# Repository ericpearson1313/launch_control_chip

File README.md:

# launch_chip
A model rocket launch control chip. A better push button?

## Datasheet
Semiconductors start out as an idea. Early datasheets allow exploration of the functionallity to meet the system need.
I've created a mock datasheet for a launch control chip, to both inspire and try to ground my design as a practical device with multiple applications.
Key functions and parameters set and documented. A compact module was defined which encompassed core functionallity centered around the device. Considering
multiple applications for this module firmed up the I/O to ease integration with clean schematics for each situation. A development board was then designed,
fully integration the LCC into a single board handheld lauch controller, and enabling chip development.

[Datasheet](Launch_chip_arch.pdf)

## Development Board PCB Design
Guided by the datasheet thought process the development board PCB was designed. The KiCad schematic and pcb have been developed and added to the repo.
The design will be revisioned until tapeout release. I'll use this board to bring up the LCC.

[KiCAD Project](dev_board.kicad_pro)

[KiCAD Schematic](dev_board.kicad_sch)

[KiCAD PCB](dev_board.kicad_pcb)

[Bill of Materials](dev_board.csv)

## Datasheet Snapshots

#### Extra prototype devices 

I have finished development of my 'perfect?' handheld launch controller powered by the launch control chip. Of the prototype run of devices I have a few extra, and have listed them for sale at cost on Ebay for an offer of $35, with free lettermail shipping. If you have followed the same technical direction as myself, I know this chip would have helped me alot, so maybe it could help other similar hobby technical enthusiasts. [LCC-01 Ebay listing](https://www.ebay.ca/itm/157937950540)

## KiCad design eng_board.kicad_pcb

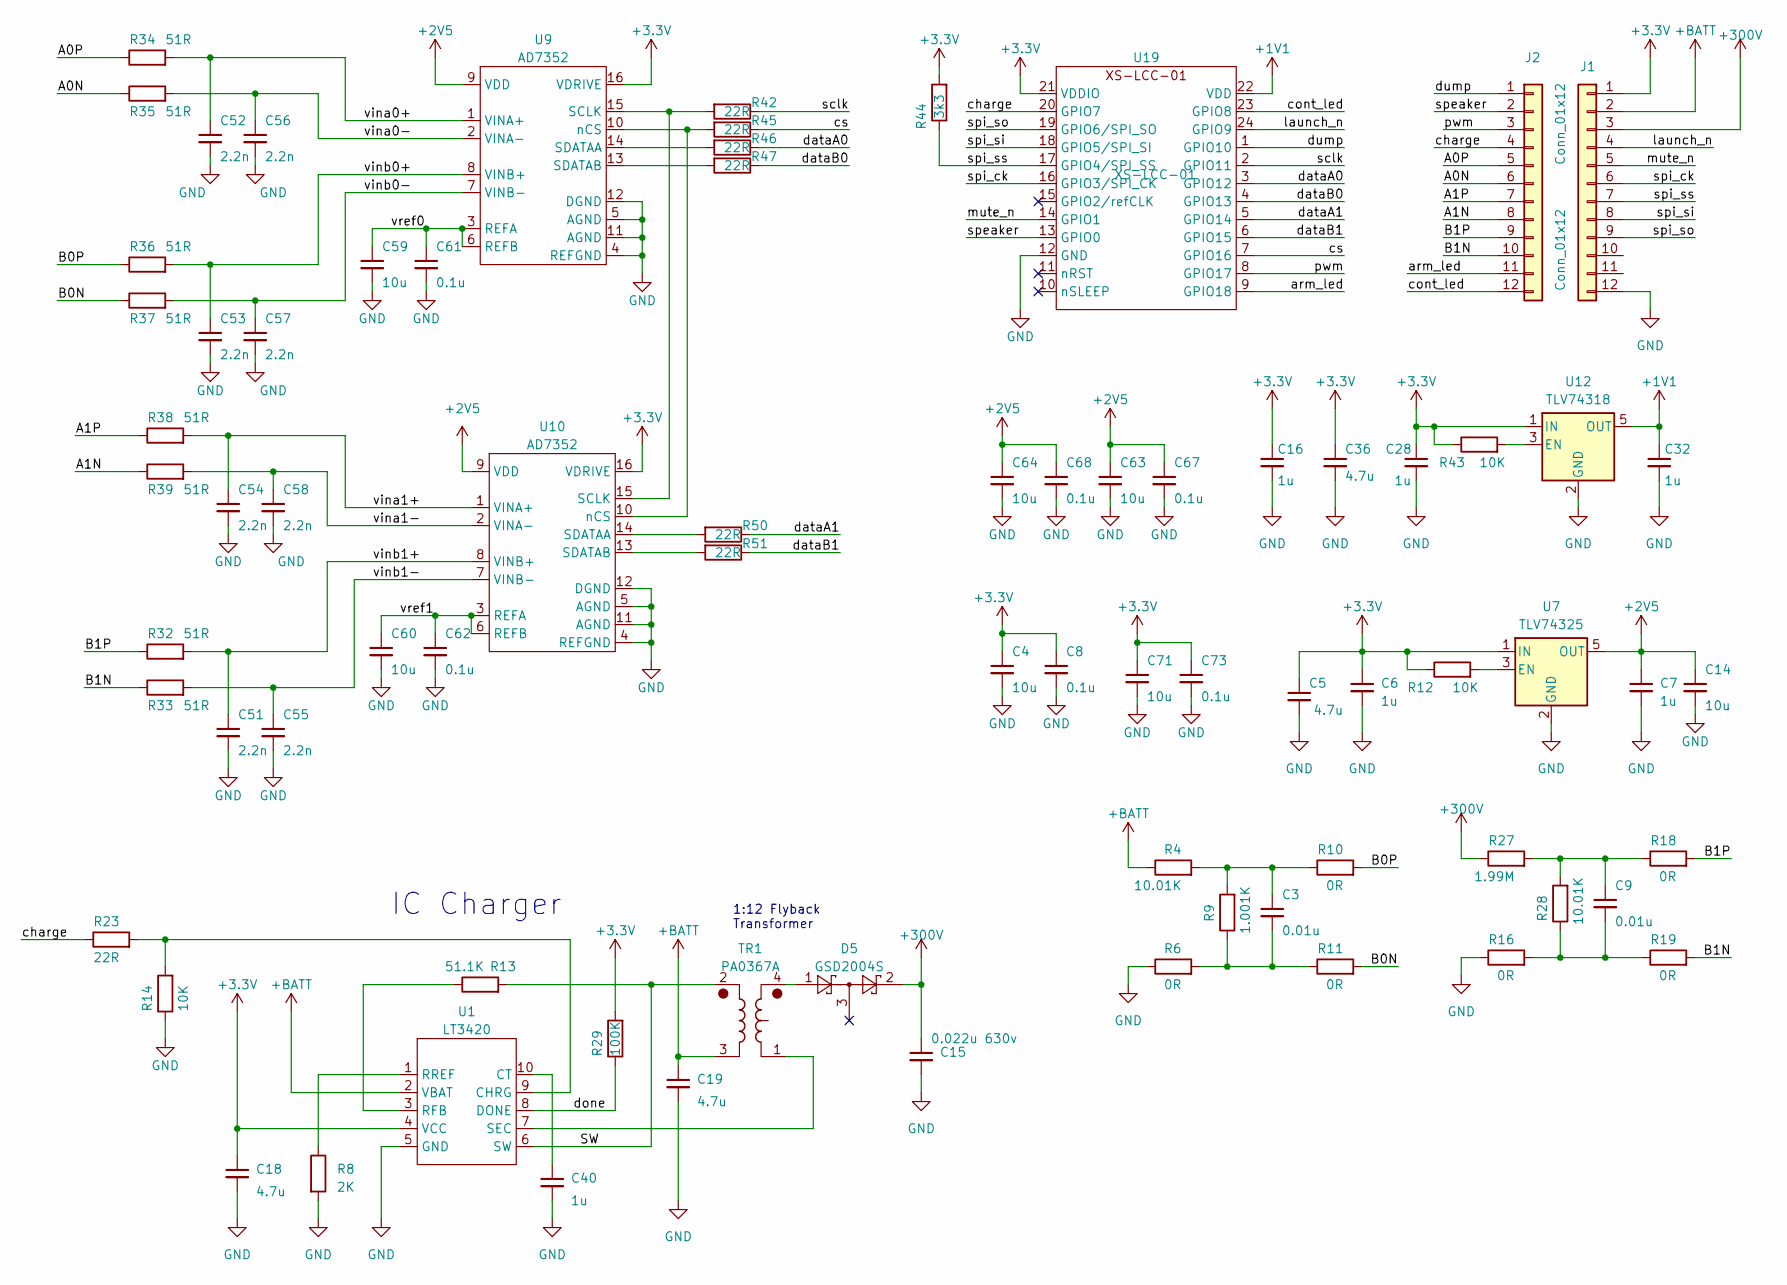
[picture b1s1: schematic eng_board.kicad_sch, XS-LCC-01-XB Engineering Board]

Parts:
C3, C9: 0.01u; C_0603_1608Metric
C4, C14, C59, C60, C63, C64, C71: 10u; C_1206_3216Metric
C5, C18, C19, C36: 4.7u; C_1206_3216Metric
C6, C7, C16, C28, C32, C40: 1u; C_0603_1608Metric
C8, C61, C62, C67, C68, C73: 0.1u; C_0603_1608Metric
C15: 0.022u 630v; C_1206_3216Metric
C51, C52, C53, C54, C55, C56, C57, C58: 2.2n; C_0603_1608Metric
D5: GSD2004S; SOT-23; JLC C85606
J1, J2: Conn_01x12; PinHeader_1x12_P2.54mm_Vertical
R4, R28: 10.01K; R_0603_1608Metric; JLC C778416
R6, R10, R11, R16, R18, R19: 0R; R_0603_1608Metric; JLC C778416
R8: 2K; R_0603_1608Metric; JLC C319700
R9: 1.001K; R_0603_1608Metric; JLC C778416
R12, R43: 10K; R_0603_1608Metric; JLC C778416
R13: 51.1K; R_0603_1608Metric; JLC C234563
R14: 10K; R_0603_1608Metric; JLC C491211
R23: 22R; R_0603_1608Metric; JLC C778416
R27: 1.99M; R_0603_1608Metric; JLC C778416
R29: 100K; R_0603_1608Metric; JLC C319967
R32, R33, R34, R35, R36, R37, R38, R39: 51R; R_0603_1608Metric; JLC C778416
R42, R45, R46, R47, R50, R51: 22R; R_0603_1608Metric; JLC C319967
R44: 3k3; R_0603_1608Metric; JLC C319967
TR1: PA0367A; PA0637A Pulse Coil 3D; JLC C5382098
U1: LT3420; MSOP-10_3x3mm_P0.5mm; JLC C670531
U7: TLV74325; SOT-23-5
U9, U10: AD7352; TSSOP-16_4.4x5mm_P0.65mm
U12: TLV74318; SOT-23-5
U19: XS-LCC-01; QFN-24-3x3mm

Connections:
+1V1: C32.1, U12.5 (OUT), U19.22 (VDD)
+2V5: C7.1, C14.1, C63.1, C64.1, C67.1, C68.1, U7.5 (OUT), U9.9 (VDD), U10.9 (VDD)
+3.3V: C4.1, C5.1, C6.1, C8.1, C16.1, C18.1, C28.1, C36.1, C71.1, C73.1, J1.1, R12.1, R29.2, R43.1, R44.2, U1.4 (VCC), U7.1 (IN), U9.16 (VDRIVE), U10.16 (VDRIVE), U12.1 (IN), U19.21 (VDDIO)
+300V: C15.1, D5.2 (NC), J1.3, R27.1
+BATT: C19.1, J1.2, R4.1, TR1.3, U1.2 (VBAT)
/A0N: J2.6, R35.1
/A0P: J2.5, R34.1
/A1N: J2.8, R39.1
/A1P: J2.7, R38.1
/B0N: R11.2, R37.1
/B0P: R10.2, R36.1
/B1N: J2.10, R19.2, R33.1
/B1P: J2.9, R18.2, R32.1
/SW: R13.2, TR1.2, U1.6 (SW)
/arm_led: J2.11, U19.9 (GPIO18)
/charge: J2.4, R23.1, U19.20 (GPIO7)
/cont_led: J2.12, U19.23 (GPIO8)
/cs: R45.1, U19.7 (GPIO16)
/dataA0: R46.1, U19.3 (GPIO12)
/dataA1: R50.1, U19.5 (GPIO14)
/dataB0: R47.1, U19.4 (GPIO13)
/dataB1: R51.1, U19.6 (GPIO15)
/done: R29.1, U1.8 (DONE)
/dump: J2.1, U19.1 (GPIO10)
/launch_n: J1.4, U19.24 (GPIO9)
/mute_n: J1.5, U19.14 (GPIO1)
/pwm: J2.3, U19.8 (GPIO17)
/sclk: R42.1, U19.2 (GPIO11)
/speaker: J2.2, U19.13 (GPIO0)
/spi_ck: J1.6, U19.16 (GPIO3/SPI_CK)
/spi_si: J1.8, U19.18 (GPIO5/SPI_SI)
/spi_so: J1.9, U19.19 (GPIO6/SPI_SO)
/spi_ss: J1.7, R44.1, U19.17 (GPIO4/SPI_SS)
/vina0+: C52.1, R34.2, U9.1 (VINA+)
/vina0-: C56.1, R35.2, U9.2 (VINA-)
/vina1+: C54.1, R38.2, U10.1 (VINA+)
/vina1-: C58.1, R39.2, U10.2 (VINA-)
/vinb0+: C53.1, R36.2, U9.8 (VINB+)
/vinb0-: C57.1, R37.2, U9.7 (VINB-)
/vinb1+: C51.1, R32.2, U10.8 (VINB+)
/vinb1-: C55.1, R33.2, U10.7 (VINB-)
/vref0: C59.1, C61.1, U9.3 (REFA), U9.6 (REFB)
/vref1: C60.1, C62.1, U10.3 (REFA), U10.6 (REFB)
GND: C4.2, C5.2, C6.2, C7.2, C8.2, C14.2, C15.2, C16.2, C18.2, C19.2, C28.2, C32.2, C36.2, C40.2, C51.2, C52.2, C53.2, C54.2, C55.2, C56.2, C57.2, C58.2, C59.2, C60.2, C61.2, C62.2, C63.2, C64.2, C67.2, C68.2, C71.2, C73.2, J1.12, R6.1, R8.2, R14.1, R16.1, U1.5 (GND), U7.2 (GND), U9.4 (REFGND), U9.5 (AGND), U9.11 (AGND), U9.12 (DGND), U10.4 (REFGND), U10.5 (AGND), U10.11 (AGND), U10.12 (DGND), U12.2 (GND), U19.12 (GND)
unnamed: C3.1, R4.2, R9.2, R10.1
unnamed: C3.2, R6.2, R9.1, R11.1
unnamed: C9.1, R18.1, R27.2, R28.2
unnamed: C9.2, R16.2, R19.1, R28.1
unnamed: D5.1, TR1.4
unnamed: R14.2, R23.2, U1.9 (CHRG)
unnamed: C40.1, U1.10 (CT)
unnamed: R13.1, U1.3 (RFB)
unnamed: R8.1, U1.1 (RREF)
unnamed: TR1.1, U1.7 (SEC)
unnamed: R12.2, U7.3 (EN)
unnamed: R46.2, U9.14 (SDATAA)
unnamed: R47.2, U9.13 (SDATAB)
unnamed: R42.2, U9.15 (SCLK), U10.15 (SCLK)
unnamed: R50.2, U10.14 (SDATAA)
unnamed: R51.2, U10.13 (SDATAB)
unnamed: R45.2, U9.10 (nCS), U10.10 (nCS)
unnamed: R43.2, U12.3 (EN)

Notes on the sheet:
IC Charger
1:12 Flyback Transformer

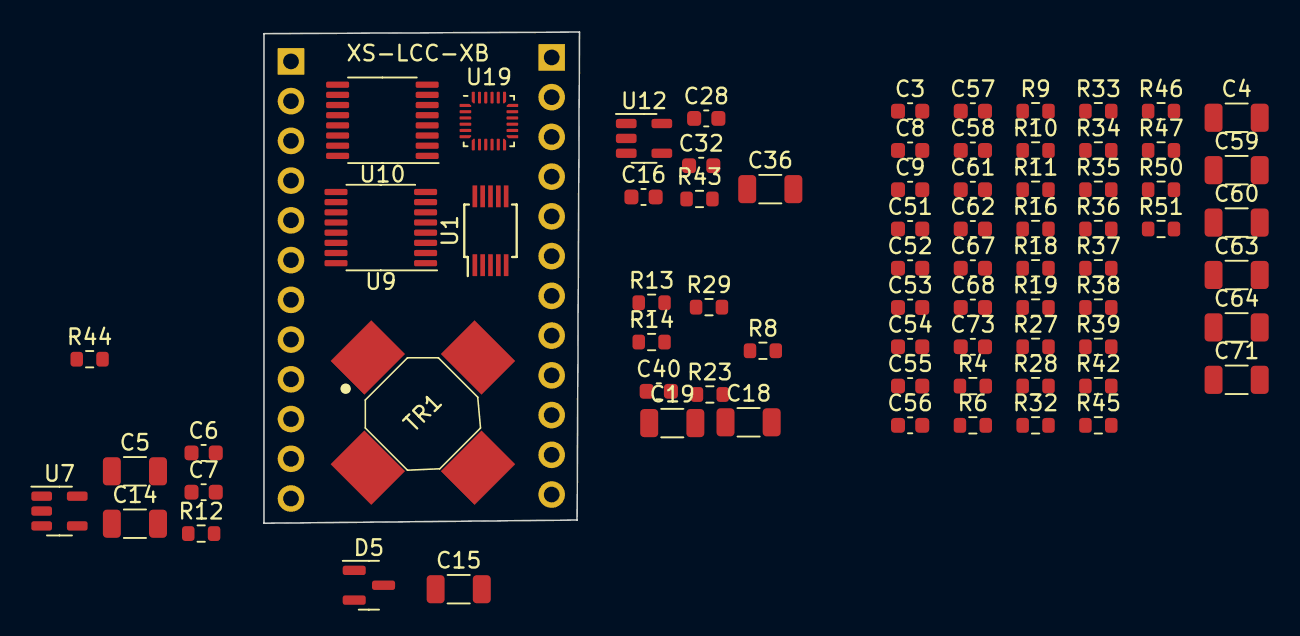
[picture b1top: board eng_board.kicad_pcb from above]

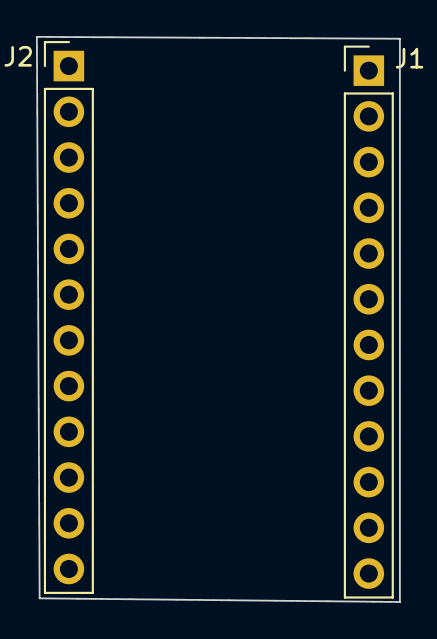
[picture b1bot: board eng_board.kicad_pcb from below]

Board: 6 copper layers, 20.2 x 31.4 mm, 76 parts (2 on the bottom side), 62 nets.
